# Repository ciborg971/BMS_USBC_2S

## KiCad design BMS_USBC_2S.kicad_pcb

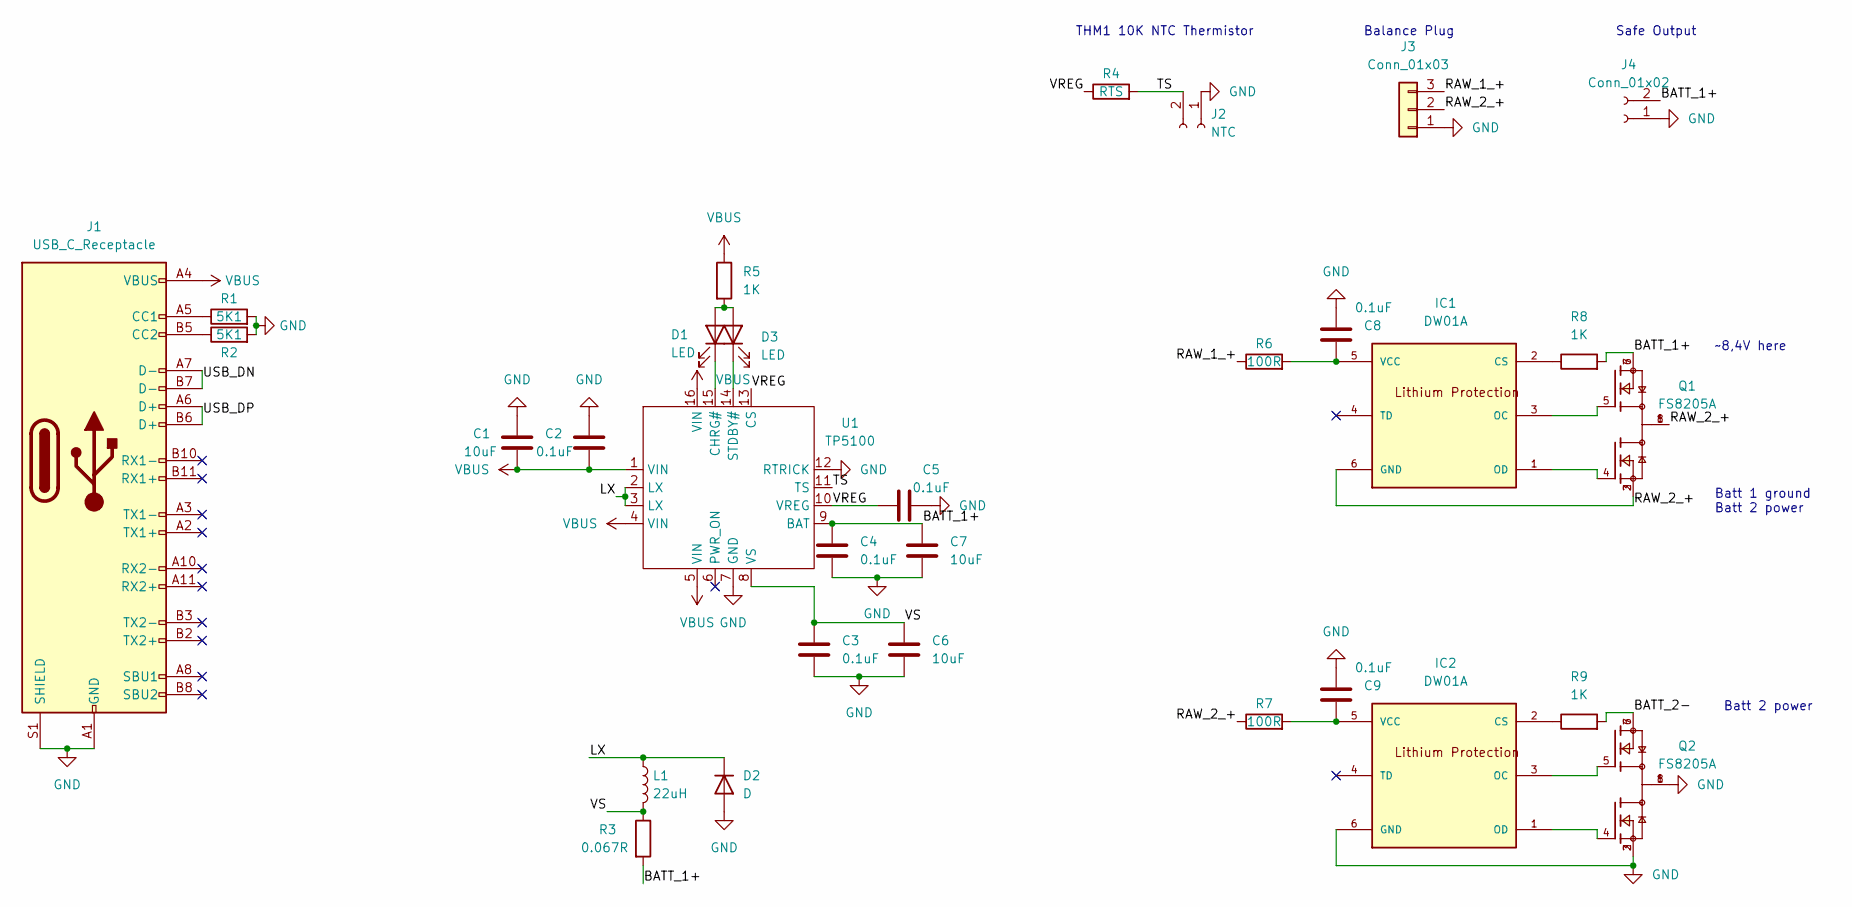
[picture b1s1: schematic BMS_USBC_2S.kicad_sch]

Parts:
C1, C6, C7: 10uF; C_0805_2012Metric
C2, C3, C4, C5, C8, C9: 0.1uF; C_0805_2012Metric
D1, D3: LED; LED_0603_1608Metric
D2: D; D_SMA-SMB_Universal_Handsoldering; LCSC C3011099
IC1, IC2: DW01A; SOT23-6; MPN DW01A; LCSC C351410
J1: USB_C_Receptacle; USB_C_Receptacle_Amphenol_12401610E4-2A
J2: NTC; PinSocket_1x02_P2.54mm_Vertical
J3: Conn_01x03; PinHeader_1x03_P2.54mm_Vertical
J4: Conn_01x02; PinSocket_1x02_P2.54mm_Vertical
L1: 22uH; MDA7030-220M; LCSC C2847487
Q1, Q2: FS8205A; SOP65P640X120-8N; PARTREV 1.7; LCSC C2830320
R1, R2: 5K1; R_0805_2012Metric
R3: 0.067R; R_0805_2012Metric
R4: RTS; R_0805_2012Metric
R5, R8, R9: 1K; R_0805_2012Metric
R6, R7: 100R; R_0805_2012Metric
U1: TP5100; QFN-16_EP_3.9x3.9_Pitch0.65mm

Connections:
/BATT_1+: C4.1, C7.1, J4.2, Q1.6, Q1.7, R3.2, R8.2, U1.9 (BAT)
/BATT_2-: Q2.6, Q2.7, R9.2
/LX: D2.1 (K), L1.1, U1.2 (LX), U1.3 (LX)
/RAW_1_+: J3.3, R6.1
/RAW_2_+: IC1.6 (GND), J3.2, Q1.1, Q1.2, Q1.3, Q1.8, R7.1
/TS: J2.2, R4.2, U1.11 (TS)
/USB_DN: J1.A7 (D-), J1.B7 (D-)
/USB_DP: J1.A6 (D+), J1.B6 (D+)
/VREG: C5.1, R4.1, U1.10 (VREG), U1.13 (CS)
/VS: C3.1, C6.1, L1.2, R3.1, U1.8 (VS)
GND: C1.1, C2.1, C3.2, C4.2, C5.2, C6.2, C7.2, C8.1, C9.1, D2.2 (A), IC2.6 (GND), J1.A1 (GND), J1.A12 (GND), J1.B1 (GND), J1.B12 (GND), J1.S1 (SHIELD), J2.1, J3.1, J4.1, Q2.1, Q2.2, Q2.3, Q2.8, R1.2, R2.2, U1.7 (GND), U1.12 (RTRICK)
unnamed: C8.2, IC1.5 (VCC), R6.2
unnamed: C9.2, IC2.5 (VCC), R7.2
unnamed: D1.1 (K), U1.15 (CHRG#)
unnamed: D1.2 (A), D3.2 (A), R5.2
unnamed: D3.1 (K), U1.14 (STDBY#)
unnamed: IC1.1 (OD), Q1.4
unnamed: IC1.2 (CS), R8.1
unnamed: IC1.3 (OC), Q1.5
unnamed: IC2.1 (OD), Q2.4
unnamed: IC2.2 (CS), R9.1
unnamed: IC2.3 (OC), Q2.5
unnamed: J1.A5 (CC1), R1.1
unnamed: J1.B5 (CC2), R2.1
VBUS: C1.2, C2.2, J1.A4 (VBUS), J1.A9 (VBUS), J1.B4 (VBUS), J1.B9 (VBUS), R5.1, U1.1 (VIN), U1.4 (VIN), U1.5 (VIN), U1.16 (VIN)

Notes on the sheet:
~8,4V here
Safe Output
THM1 10K NTC Thermistor
Balance Plug
Batt 2 power
Batt 1 ground Batt 2 power

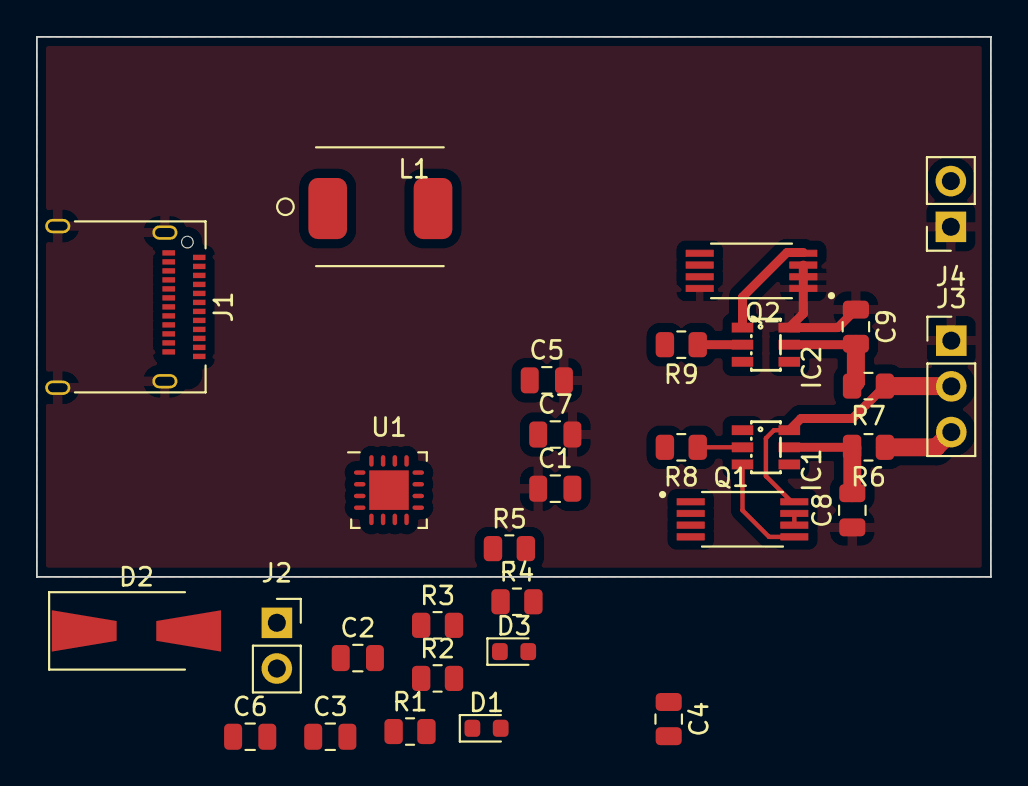
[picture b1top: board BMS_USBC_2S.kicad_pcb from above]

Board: 2 copper layers, 53.0 x 30.0 mm, 31 parts (0 on the bottom side), 25 nets.

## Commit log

2022-08-31 Add schematic
2022-08-31 Add documentation about TP5100 and DW01
2022-08-31 Add pcb and power output connector
